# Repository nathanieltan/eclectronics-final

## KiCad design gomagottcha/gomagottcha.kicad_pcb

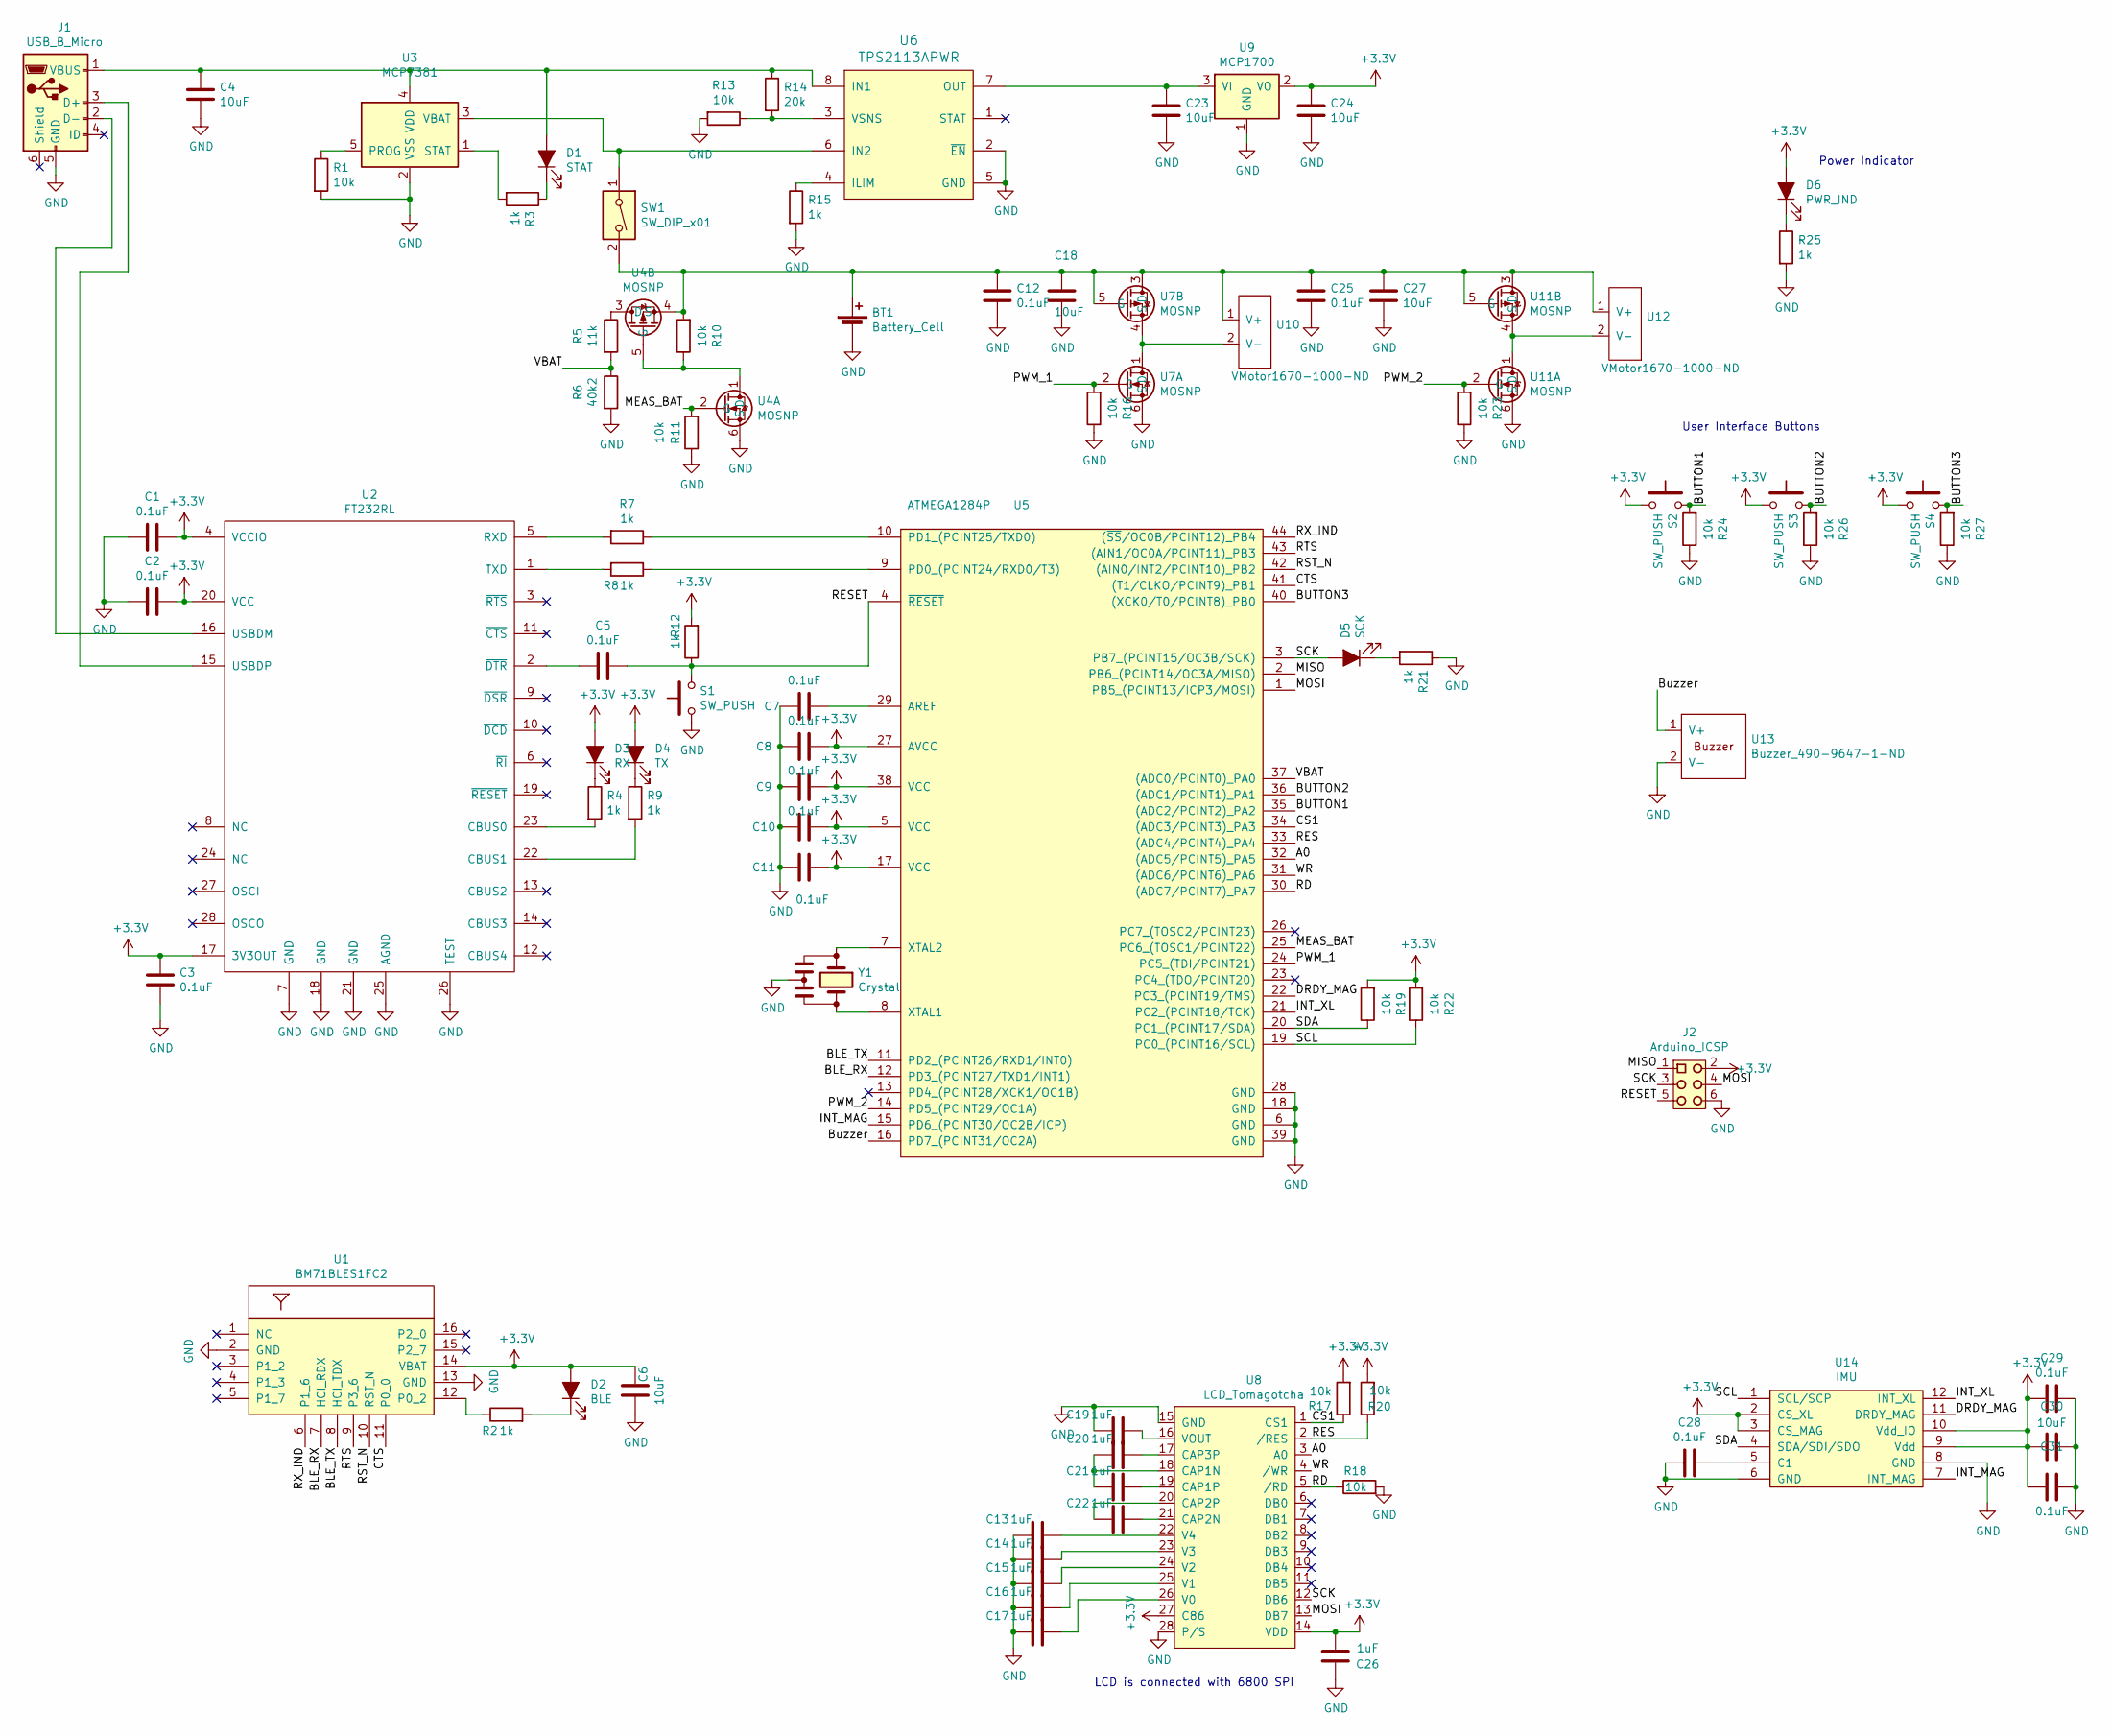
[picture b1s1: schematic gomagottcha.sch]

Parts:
BT1: Battery_Cell; PhoenixContact_MSTBVA_2,5_2-G_1x02_P5.00mm_Vertical
C1, C2, C3, C5, C7, C8, C9, C10, C11, C12, C25, C28, C29, C31: 0.1uF; C_0603_1608Metric
C4, C6, C18, C23, C24, C27, C30: 10uF; C_0603_1608Metric
C13, C14, C15, C16, C17, C19, C20, C21, C22, C26: 1uF; C_0603_1608Metric
D1: STAT; LED_0603_1608Metric
D2: BLE; LED_0603_1608Metric
D3: RX; LED_0603_1608Metric
D4: TX; LED_0603_1608Metric
D5: SCK; LED_0603_1608Metric
D6: PWR_IND; LED_0603_1608Metric
J1: USB_B_Micro; USB micro 609-4616-1-ND
J2: Arduino_ICSP
R1, R10, R11, R13, R16, R17, R18, R19, R20, R22, R23, R24, R26, R27: 10k; R_0603_1608Metric
R2, R3, R4, R7, R8, R9, R12, R15, R21, R25: 1k; R_0603_1608Metric
R5: 11k; R_0603_1608Metric
R6: 40k2; R_0603_1608Metric
R14: 20k; R_0603_1608Metric
S1, S2, S3, S4: SW_PUSH; Pushbutton_EG4791-ND
SW1: SW_DIP_x01; Switch_CWI333-ND
U1: BM71BLES1FC2; BM71BLE
U2: FT232RL; SSOP-28_5.3x10.2mm_P0.65mm
U3: MCP7381; SOT-23-5
U4, U7, U11: MOSNP; SOT-363_SC-70-6
U5: ATMEGA1284P; TQFP-44_10x10mm_P0.8mm
U6: TPS2113APWR; TSSOP-8_4.4x3mm_P0.65mm
U8: LCD_Tomagotcha; LCD NHD-C12864LZ-FSW-FBW-3V3-ND
U9: MCP1700; SOT-23
U10, U12: VMotor1670-1000-ND; VMotor 1670-1000-ND
U13: Buzzer_490-9647-1-ND; Buzzer 490-9647-1-ND
U14: IMU
Y1: Crystal; 8MHz_Crystal

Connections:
+3V3: C1.1, C2.1, C3.2, C6.1, C8.1, C9.1, C10.1, C11.1, C24.1, C26.1, C29.2, C30.2, C31.2, D2.2 (A), D3.2 (A), D4.2 (A), D6.2 (A), J2.2, R12.2, R17.2, R19.2, R20.2, R22.2, S2.1, S3.1, S4.1, U1.14 (VBAT), U2.4 (VCCIO), U2.17 (3V3OUT), U2.20 (VCC), U5.5 (VCC), U5.17 (VCC), U5.27 (AVCC), U5.38 (VCC), U8.14 (VDD), U8.27 (C86), U9.2 (VO), U14.2 (CS_XL), U14.3 (CS_MAG), U14.9 (Vdd), U14.10 (Vdd_IO)
/A0: U5.32 ((ADC5/PCINT5)_PA5), U8.3 (A0)
/BLE_RX: U1.7 (HCI_RDX), U5.12 (PD3_(PCINT27/TXD1/INT1))
/BLE_TX: U1.8 (HCI_TDX), U5.11 (PD2_(PCINT26/RXD1/INT0))
/BUTTON1: R24.2, S2.2, U5.35 ((ADC2/PCINT2)_PA2)
/BUTTON2: R26.2, S3.2, U5.36 ((ADC1/PCINT1)_PA1)
/BUTTON3: R27.2, S4.2, U5.40 ((XCK0/T0/PCINT8)_PB0)
/Buzzer: U5.16 (PD7_(PCINT31/OC2A)), U13.1 (V+)
/CS1: R17.1, U5.34 ((ADC3/PCINT3)_PA3), U8.1 (CS1)
/CTS: U1.11 (P0_0), U5.41 ((T1/CLKO/PCINT9)_PB1)
/DRDY_MAG: U5.22 (PC3_(PCINT19/TMS)), U14.11 (DRDY_MAG)
/INT_MAG: U5.15 (PD6_(PCINT30/OC2B/ICP)), U14.7 (INT_MAG)
/INT_XL: U5.21 (PC2_(PCINT18/TCK)), U14.12 (INT_XL)
/MEAS_BAT: R11.2, U4.2 (G), U5.25 (PC6_(TOSC1/PCINT22))
/MISO: J2.1, U5.2 (PB6_(PCINT14/OC3A/MISO))
/MOSI: J2.4, U5.1 (PB5_(PCINT13/ICP3/MOSI)), U8.13 (DB7)
/PWM_1: R16.2, U5.24 (PC5_(TDI/PCINT21)), U7.2 (G)
/PWM_2: R23.2, U5.14 (PD5_(PCINT29/OC1A)), U11.2 (G)
/RD: R18.1, U5.30 ((ADC7/PCINT7)_PA7), U8.5 (/RD)
/RES: R20.1, U5.33 ((ADC4/PCINT4)_PA4), U8.2 (/RES)
/RESET: C5.1, J2.5, R12.1, S1.2, U5.4 (~RESET)
/RST_N: U1.10 (RST_N), U5.42 ((AIN0/INT2/PCINT10)_PB2)
/RTS: U1.9 (P3_6), U5.43 ((AIN1/OC0A/PCINT11)_PB3)
/RX_IND: U1.6 (P1_6), U5.44 ((~SS~/OC0B/PCINT12)_PB4)
/SCK: D5.2 (A), J2.3, U5.3 (PB7_(PCINT15/OC3B/SCK)), U8.12 (DB6)
/SCL: R22.1, U5.19 (PC0_(PCINT16/SCL)), U14.1 (SCL/SCP)
/SDA: R19.1, U5.20 (PC1_(PCINT17/SDA)), U14.4 (SDA/SDI/SDO)
/VBAT: R5.2, R6.1, U5.37 ((ADC0/PCINT0)_PA0)
/WR: U5.31 ((ADC6/PCINT6)_PA6), U8.4 (/WR)
GND: BT1.2 (-), C1.2, C2.2, C3.1, C4.2, C6.2, C7.2, C8.2, C9.2, C10.2, C11.2, C12.2, C13.2, C14.2, C15.2, C16.2, C17.2, C18.2, C19.2, C23.2, C24.2, C25.2, C26.2, C27.2, C28.2, C29.1, C30.1, C31.1, J1.5 (GND), J2.6, R1.2, R6.2, R11.1, R13.2, R15.2, R16.1, R18.2, R21.1, R23.1, R24.1, R25.2, R26.1, R27.1, S1.1, U1.2 (GND), U1.13 (GND), U2.7 (GND), U2.18 (GND), U2.21 (GND), U2.25 (AGND), U2.26 (TEST), U3.2 (VSS), U4.6 (S), U5.6 (GND), U5.18 (GND), U5.28 (GND), U5.39 (GND), U6.2 (~EN), U6.5 (GND), U7.6 (S), U8.15 (GND), U8.28 (P/S), U9.1 (GND), U11.6 (S), U13.2 (V-), U14.6 (GND), U14.8 (GND), Y1.2
unnamed: BT1.1 (+), C12.1, C18.1, C25.1, C27.1, R10.2, SW1.2, U4.4 (S), U7.3 (D), U7.5 (G), U10.1 (V+), U11.3 (D), U11.5 (G), U12.1 (V+)
unnamed: C4.1, D1.2 (A), J1.1 (VBUS), R14.1, U3.4 (VDD), U6.8 (IN1)
unnamed: C5.2, U2.2 (~DTR)
unnamed: C7.1, U5.29 (AREF)
unnamed: C13.1, U8.22 (V4)
unnamed: C14.1, U8.23 (V3)
unnamed: C15.1, U8.24 (V2)
unnamed: C16.1, U8.25 (V1)
unnamed: C17.1, U8.26 (V0)
unnamed: C19.1, U8.16 (VOUT)
unnamed: C20.1, U8.17 (CAP3P)
unnamed: C20.2, C21.2, U8.18 (CAP1N)
unnamed: C21.1, U8.19 (CAP1P)
unnamed: C22.1, U8.21 (CAP2N)
unnamed: C22.2, U8.20 (CAP2P)
unnamed: C23.1, U6.7 (OUT), U9.3 (VI)
unnamed: C28.1, U14.5 (C1)
unnamed: D1.1 (K), R3.1
unnamed: D2.1 (K), R2.2
unnamed: D3.1 (K), R4.1
unnamed: D4.1 (K), R9.1
unnamed: D5.1 (K), R21.2
unnamed: D6.1 (K), R25.1
unnamed: J1.2 (D-), U2.16 (USBDM)
unnamed: J1.3 (D+), U2.15 (USBDP)
unnamed: R1.1, U3.5 (PROG)
unnamed: R2.1, U1.12 (P0_2)
unnamed: R3.2, U3.1 (STAT)
unnamed: R4.2, U2.23 (CBUS0)
unnamed: R5.1, U4.3 (D)
unnamed: R7.1, U5.10 (PD1_(PCINT25/TXD0))
unnamed: R7.2, U2.5 (RXD)
unnamed: R8.1, U5.9 (PD0_(PCINT24/RXD0/T3))
unnamed: R8.2, U2.1 (TXD)
unnamed: R9.2, U2.22 (CBUS1)
unnamed: R10.1, U4.1 (D), U4.5 (G)
unnamed: R13.1, R14.2, U6.3 (VSNS)
unnamed: R15.1, U6.4 (ILIM)
unnamed: SW1.1, U3.3 (VBAT), U6.6 (IN2)
unnamed: U5.7 (XTAL2), Y1.1
unnamed: U5.8 (XTAL1), Y1.3
unnamed: U7.1 (D), U7.4 (S), U10.2 (V-)
unnamed: U11.1 (D), U11.4 (S), U12.2 (V-)

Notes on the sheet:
LCD is connected with 6800 SPI
User Interface Buttons
Power Indicator

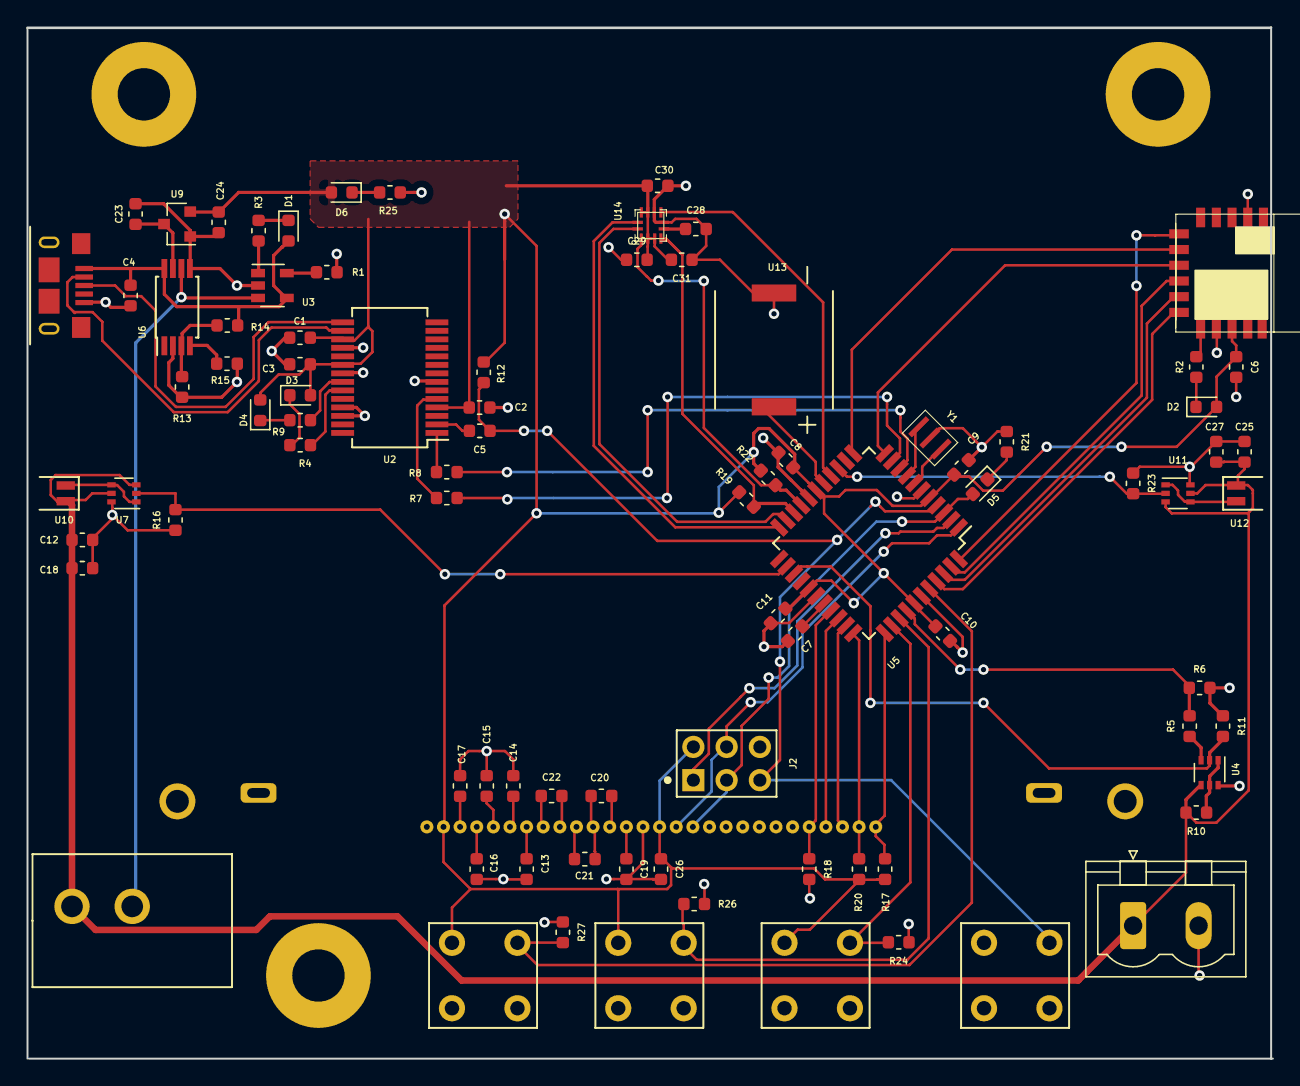
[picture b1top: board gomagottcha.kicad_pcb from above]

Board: 2 copper layers, 95.1 x 78.7 mm, 87 parts (0 on the bottom side), 73 nets.

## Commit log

2019-03-28 Initialized KiCad Project
2019-03-28 Initialized symbol library
2019-03-28 Create library with IMU footprint
2019-03-28 Change IMU footprint from mechanical to footprint
2019-03-28 Add LDC footprint
2019-03-30 syncing
2019-04-01 Add symbol for LCD; correct pinout of LCD footprint
2019-04-01 new symbol library
2019-04-01 fixed tama-sym
2019-04-01 Add footprint for USB connector
2019-04-01 Correct pin numbers on USB footprint
2019-04-01 Add BLE footprint
2019-04-03 sync
2019-04-03 Add footprint for vibration motor
2019-04-03 Add symbol for vibration motor
2019-04-03 started schematic
2019-04-03 updated schematic
2019-04-04 Add BM71BLES1FC2 symbol
2019-04-05 Add buzzer symbol and footprint
2019-04-05 LCD and IMU hooked up
2019-04-05 Add 8MHz crystal footprint
2019-04-05 Add some footprints to symbols
2019-04-05 Add more footprints to schematic
2019-04-05 Change atmega1284 symbol from PDIP to TGFP
2019-04-08 Update page size on schematic
2019-04-08 Add footprint and symbol for pushbutton
2019-04-08 Footprint and symbol for slide switch
2019-04-08 BLE hooked up
2019-04-09 TO DO: Finish assigning footprints
2019-04-10 TODO: replace FT232R symbol
2019-04-10 Changed TCSP symbol from QFN to QFP
2019-04-11 Footprints are done, TODO: Layout
2019-04-11 Add stockroom pushbutton footprint
2019-04-11 started layout
2019-04-13 REVERT TO THIS IF REPINNING DOESNT WORK
2019-04-13 TODO: Add screw holes and maybe picture
2019-04-15 changed all 100nF caps to 0.1uF
2019-04-16 added screw holes
